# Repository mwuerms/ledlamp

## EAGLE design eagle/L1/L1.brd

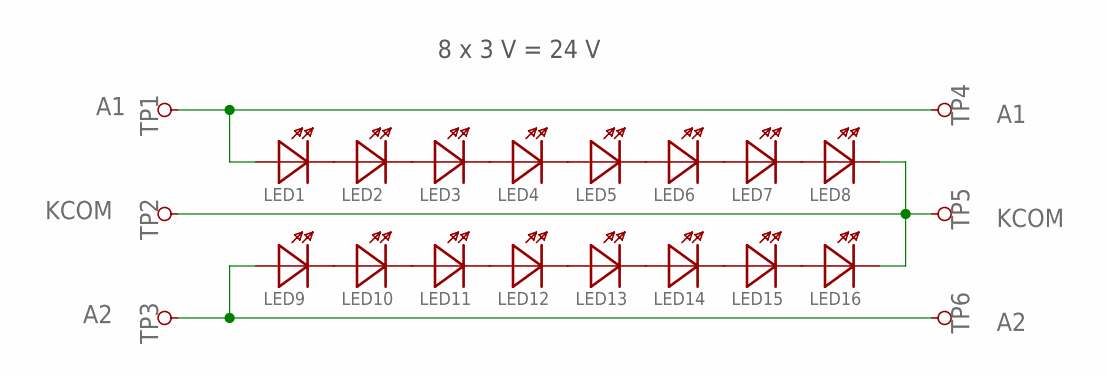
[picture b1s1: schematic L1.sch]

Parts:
LED1, LED2, LED3, LED4, LED5, LED6, LED7, LED8, LED9, LED10, LED11, LED12, LED13, LED14, LED15, LED16: LED_JE2835
TP1, TP4: A1; PAD_4X2.2MM
TP2, TP5: KCOM; PAD_4X2.2MM
TP3, TP6: A2; PAD_4X2.2MM

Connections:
A1: LED1.1 (A), TP1.1, TP4.1
A2: LED9.1 (A), TP3.1, TP6.1
KCOM: LED8.2 (K), LED16.2 (K), TP2.1, TP5.1
unnamed: LED1.2 (K), LED2.1 (A)
unnamed: LED2.2 (K), LED3.1 (A)
unnamed: LED3.2 (K), LED4.1 (A)
unnamed: LED4.2 (K), LED5.1 (A)
unnamed: LED5.2 (K), LED6.1 (A)
unnamed: LED6.2 (K), LED7.1 (A)
unnamed: LED7.2 (K), LED8.1 (A)
unnamed: LED9.2 (K), LED10.1 (A)
unnamed: LED10.2 (K), LED11.1 (A)
unnamed: LED11.2 (K), LED12.1 (A)
unnamed: LED12.2 (K), LED13.1 (A)
unnamed: LED13.2 (K), LED14.1 (A)
unnamed: LED14.2 (K), LED15.1 (A)
unnamed: LED15.2 (K), LED16.1 (A)

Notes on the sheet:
8 x 3 V = 24 V

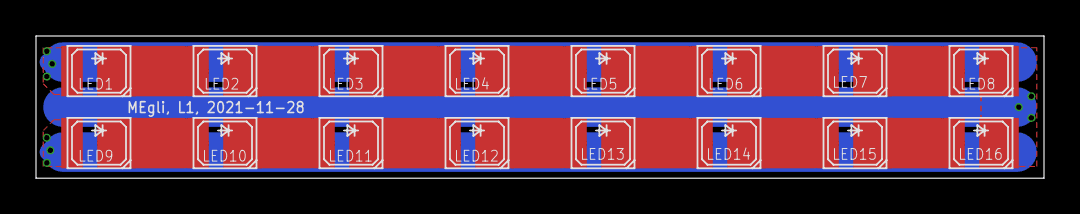
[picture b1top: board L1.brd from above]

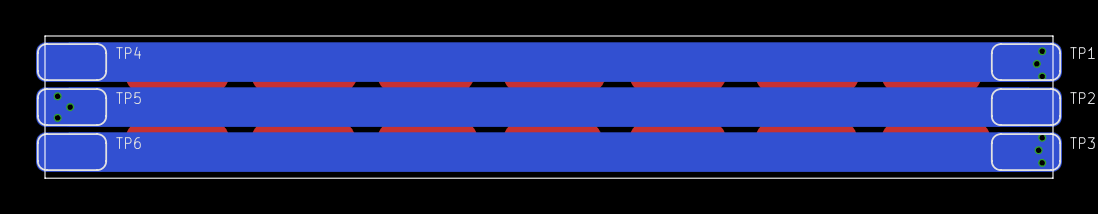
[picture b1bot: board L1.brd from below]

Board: 2 copper layers, 56.0 x 7.9 mm, 22 parts (6 on the bottom side), 17 nets.

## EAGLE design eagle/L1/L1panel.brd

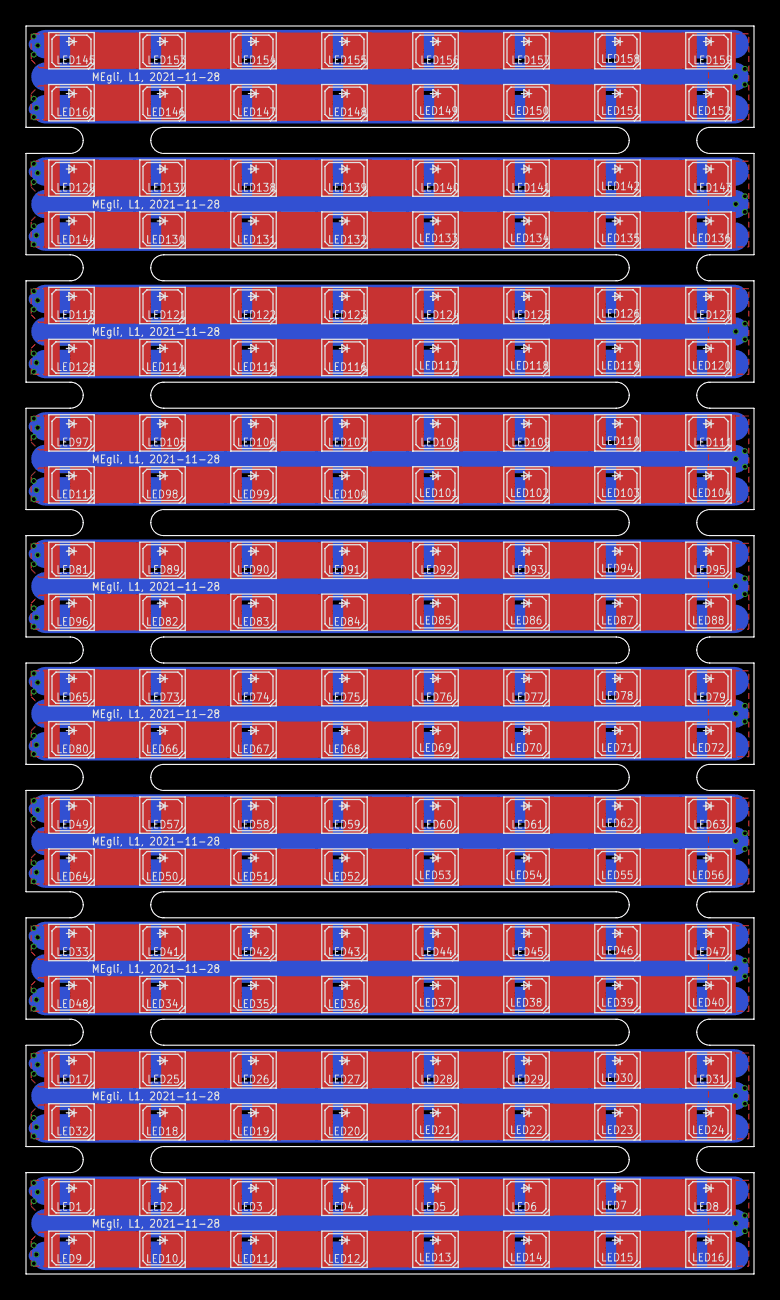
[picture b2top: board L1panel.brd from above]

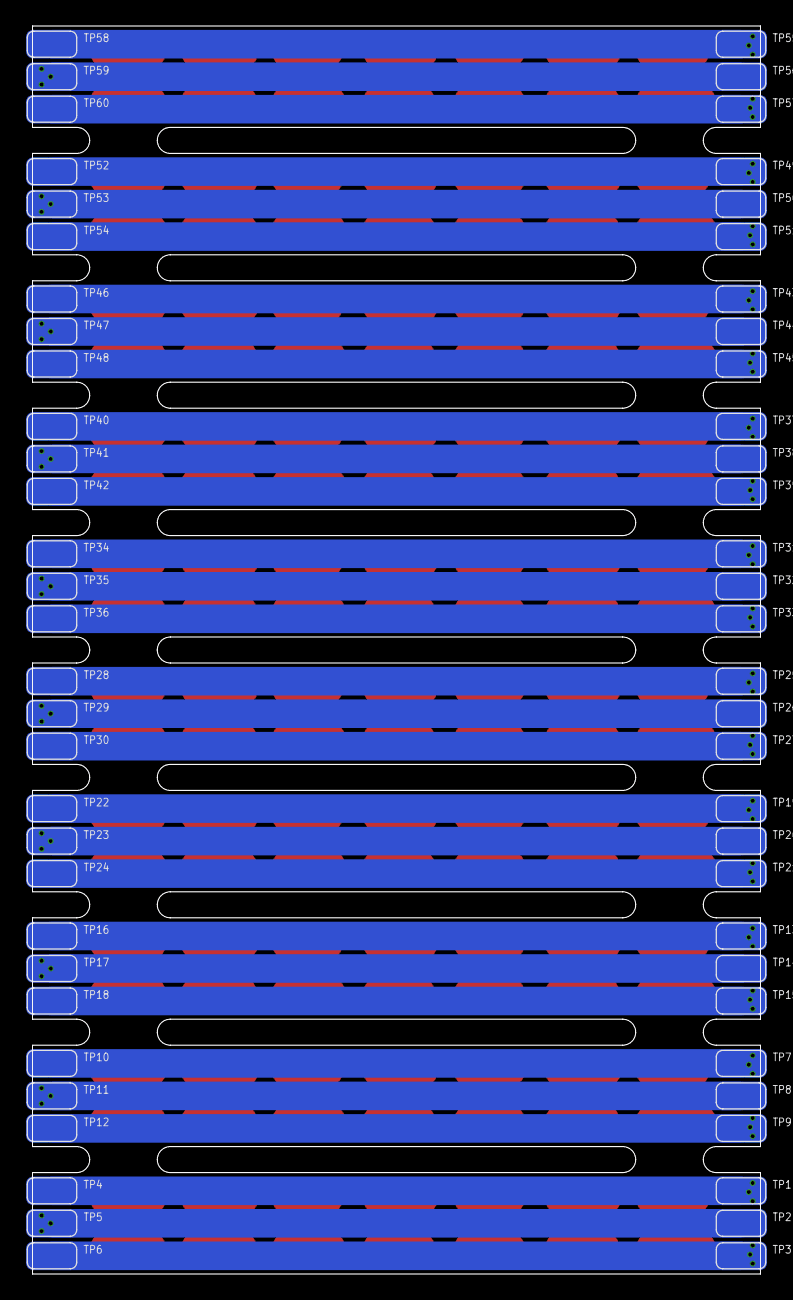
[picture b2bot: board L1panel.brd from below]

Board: 2 copper layers, 56.0 x 96.0 mm, 220 parts (60 on the bottom side), 170 nets.

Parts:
LED1, LED2, LED3, LED4, LED5, LED6, LED7, LED8, LED9, LED10, LED11, LED12, LED13, LED14, LED15, LED16, LED17, LED18, LED19, LED20, LED21, LED22, LED23, LED24, LED25, LED26, LED27, LED28, LED29, LED30, LED31, LED32, LED33, LED34, LED35, LED36, LED37, LED38, LED39, LED40, LED41, LED42, LED43, LED44, LED45, LED46, LED47, LED48, LED49, LED50, LED51, LED52, LED53, LED54, LED55, LED56, LED57, LED58, LED59, LED60, LED61, LED62, LED63, LED64, LED65, LED66, LED67, LED68, LED69, LED70, LED71, LED72, LED73, LED74, LED75, LED76, LED77, LED78, LED79, LED80, LED81, LED82, LED83, LED84, LED85, LED86, LED87, LED88, LED89, LED90, LED91, LED92, LED93, LED94, LED95, LED96, LED97, LED98, LED99, LED100, LED101, LED102, LED103, LED104, LED105, LED106, LED107, LED108, LED109, LED110, LED111, LED112, LED113, LED114, LED115, LED116, LED117, LED118, LED119, LED120, LED121, LED122, LED123, LED124, LED125, LED126, LED127, LED128, LED129, LED130, LED131, LED132, LED133, LED134, LED135, LED136, LED137, LED138, LED139, LED140, LED141, LED142, LED143, LED144, LED145, LED146, LED147, LED148, LED149, LED150, LED151, LED152, LED153, LED154, LED155, LED156, LED157, LED158, LED159, LED160: LED_JE2835
TP1, TP4, TP7, TP10, TP13, TP16, TP19, TP22, TP25, TP28, TP31, TP34, TP37, TP40, TP43, TP46, TP49, TP52, TP55, TP58: A1; PAD_4X2.2MM
TP2, TP5, TP8, TP11, TP14, TP17, TP20, TP23, TP26, TP29, TP32, TP35, TP38, TP41, TP44, TP47, TP50, TP53, TP56, TP59: KCOM; PAD_4X2.2MM
TP3, TP6, TP9, TP12, TP15, TP18, TP21, TP24, TP27, TP30, TP33, TP36, TP39, TP42, TP45, TP48, TP51, TP54, TP57, TP60: A2; PAD_4X2.2MM

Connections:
A1: LED1.1, TP1.1, TP4.1
A2: LED9.1, TP3.1, TP6.1
A3: LED17.1, TP7.1, TP10.1
A4: LED32.1, TP9.1, TP12.1
A5: LED33.1, TP13.1, TP16.1
A6: LED48.1, TP15.1, TP18.1
A7: LED49.1, TP19.1, TP22.1
A8: LED64.1, TP21.1, TP24.1
A9: LED65.1, TP25.1, TP28.1
A10: LED80.1, TP27.1, TP30.1
A11: LED81.1, TP31.1, TP34.1
A12: LED96.1, TP33.1, TP36.1
A13: LED97.1, TP37.1, TP40.1
A14: LED112.1, TP39.1, TP42.1
A15: LED113.1, TP43.1, TP46.1
A16: LED128.1, TP45.1, TP48.1
A17: LED129.1, TP49.1, TP52.1
A18: LED144.1, TP51.1, TP54.1
A19: LED145.1, TP55.1, TP58.1
A20: LED160.1, TP57.1, TP60.1
KCOM: LED8.2, LED16.2, TP2.1, TP5.1
KCOM1: LED24.2, LED31.2, TP8.1, TP11.1
KCOM2: LED40.2, LED47.2, TP14.1, TP17.1
KCOM3: LED56.2, LED63.2, TP20.1, TP23.1
KCOM4: LED72.2, LED79.2, TP26.1, TP29.1
KCOM5: LED88.2, LED95.2, TP32.1, TP35.1
KCOM6: LED104.2, LED111.2, TP38.1, TP41.1
KCOM7: LED120.2, LED127.2, TP44.1, TP47.1
KCOM8: LED136.2, LED143.2, TP50.1, TP53.1
KCOM9: LED152.2, LED159.2, TP56.1, TP59.1
unnamed: LED1.2, LED2.1
unnamed: LED2.2, LED3.1
unnamed: LED3.2, LED4.1
unnamed: LED4.2, LED5.1
unnamed: LED5.2, LED6.1
unnamed: LED6.2, LED7.1
unnamed: LED7.2, LED8.1
unnamed: LED9.2, LED10.1
unnamed: LED10.2, LED11.1
unnamed: LED11.2, LED12.1
unnamed: LED12.2, LED13.1
unnamed: LED13.2, LED14.1
unnamed: LED14.2, LED15.1
unnamed: LED15.2, LED16.1
unnamed: LED17.2, LED25.1
unnamed: LED25.2, LED26.1
unnamed: LED26.2, LED27.1
unnamed: LED27.2, LED28.1
unnamed: LED28.2, LED29.1
unnamed: LED29.2, LED30.1
unnamed: LED30.2, LED31.1
unnamed: LED18.1, LED32.2
unnamed: LED18.2, LED19.1
unnamed: LED19.2, LED20.1
unnamed: LED20.2, LED21.1
unnamed: LED21.2, LED22.1
unnamed: LED22.2, LED23.1
unnamed: LED23.2, LED24.1
unnamed: LED33.2, LED41.1
unnamed: LED41.2, LED42.1
unnamed: LED42.2, LED43.1
unnamed: LED43.2, LED44.1
unnamed: LED44.2, LED45.1
unnamed: LED45.2, LED46.1
unnamed: LED46.2, LED47.1
unnamed: LED34.1, LED48.2
unnamed: LED34.2, LED35.1
unnamed: LED35.2, LED36.1
unnamed: LED36.2, LED37.1
unnamed: LED37.2, LED38.1
unnamed: LED38.2, LED39.1
unnamed: LED39.2, LED40.1
unnamed: LED49.2, LED57.1
unnamed: LED57.2, LED58.1
unnamed: LED58.2, LED59.1
unnamed: LED59.2, LED60.1
unnamed: LED60.2, LED61.1
unnamed: LED61.2, LED62.1
unnamed: LED62.2, LED63.1
unnamed: LED50.1, LED64.2
unnamed: LED50.2, LED51.1
unnamed: LED51.2, LED52.1
unnamed: LED52.2, LED53.1
unnamed: LED53.2, LED54.1
unnamed: LED54.2, LED55.1
unnamed: LED55.2, LED56.1
unnamed: LED65.2, LED73.1
unnamed: LED73.2, LED74.1
unnamed: LED74.2, LED75.1
unnamed: LED75.2, LED76.1
unnamed: LED76.2, LED77.1
unnamed: LED77.2, LED78.1
unnamed: LED78.2, LED79.1
unnamed: LED66.1, LED80.2
unnamed: LED66.2, LED67.1
unnamed: LED67.2, LED68.1
unnamed: LED68.2, LED69.1
unnamed: LED69.2, LED70.1
unnamed: LED70.2, LED71.1
unnamed: LED71.2, LED72.1
unnamed: LED81.2, LED89.1
unnamed: LED89.2, LED90.1
unnamed: LED90.2, LED91.1
unnamed: LED91.2, LED92.1
unnamed: LED92.2, LED93.1
unnamed: LED93.2, LED94.1
unnamed: LED94.2, LED95.1
unnamed: LED82.1, LED96.2
unnamed: LED82.2, LED83.1
unnamed: LED83.2, LED84.1
unnamed: LED84.2, LED85.1
unnamed: LED85.2, LED86.1
unnamed: LED86.2, LED87.1
unnamed: LED87.2, LED88.1
unnamed: LED97.2, LED105.1
unnamed: LED105.2, LED106.1
unnamed: LED106.2, LED107.1
unnamed: LED107.2, LED108.1
unnamed: LED108.2, LED109.1
unnamed: LED109.2, LED110.1
unnamed: LED110.2, LED111.1
unnamed: LED98.1, LED112.2
unnamed: LED98.2, LED99.1
unnamed: LED99.2, LED100.1
unnamed: LED100.2, LED101.1
unnamed: LED101.2, LED102.1
unnamed: LED102.2, LED103.1
unnamed: LED103.2, LED104.1
unnamed: LED113.2, LED121.1
unnamed: LED121.2, LED122.1
unnamed: LED122.2, LED123.1
unnamed: LED123.2, LED124.1
unnamed: LED124.2, LED125.1
unnamed: LED125.2, LED126.1
unnamed: LED126.2, LED127.1
unnamed: LED114.1, LED128.2
unnamed: LED114.2, LED115.1
unnamed: LED115.2, LED116.1
unnamed: LED116.2, LED117.1
unnamed: LED117.2, LED118.1
unnamed: LED118.2, LED119.1
unnamed: LED119.2, LED120.1
unnamed: LED129.2, LED137.1
unnamed: LED137.2, LED138.1
unnamed: LED138.2, LED139.1
unnamed: LED139.2, LED140.1
unnamed: LED140.2, LED141.1
unnamed: LED141.2, LED142.1
unnamed: LED142.2, LED143.1
unnamed: LED130.1, LED144.2
unnamed: LED130.2, LED131.1
unnamed: LED131.2, LED132.1
unnamed: LED132.2, LED133.1
unnamed: LED133.2, LED134.1
unnamed: LED134.2, LED135.1
unnamed: LED135.2, LED136.1
unnamed: LED145.2, LED153.1
unnamed: LED153.2, LED154.1
unnamed: LED154.2, LED155.1
unnamed: LED155.2, LED156.1
unnamed: LED156.2, LED157.1
unnamed: LED157.2, LED158.1
unnamed: LED158.2, LED159.1
unnamed: LED146.1, LED160.2
unnamed: LED146.2, LED147.1
unnamed: LED147.2, LED148.1
unnamed: LED148.2, LED149.1
unnamed: LED149.2, LED150.1
unnamed: LED150.2, LED151.1
unnamed: LED151.2, LED152.1

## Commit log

2021-11-25 added pcb
2021-11-28 L1: in eagle7, ready to order
